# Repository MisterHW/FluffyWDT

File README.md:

# FluffyWDT
Raspberry Pi hardware watchdog with optional bluetooth SPP adapter

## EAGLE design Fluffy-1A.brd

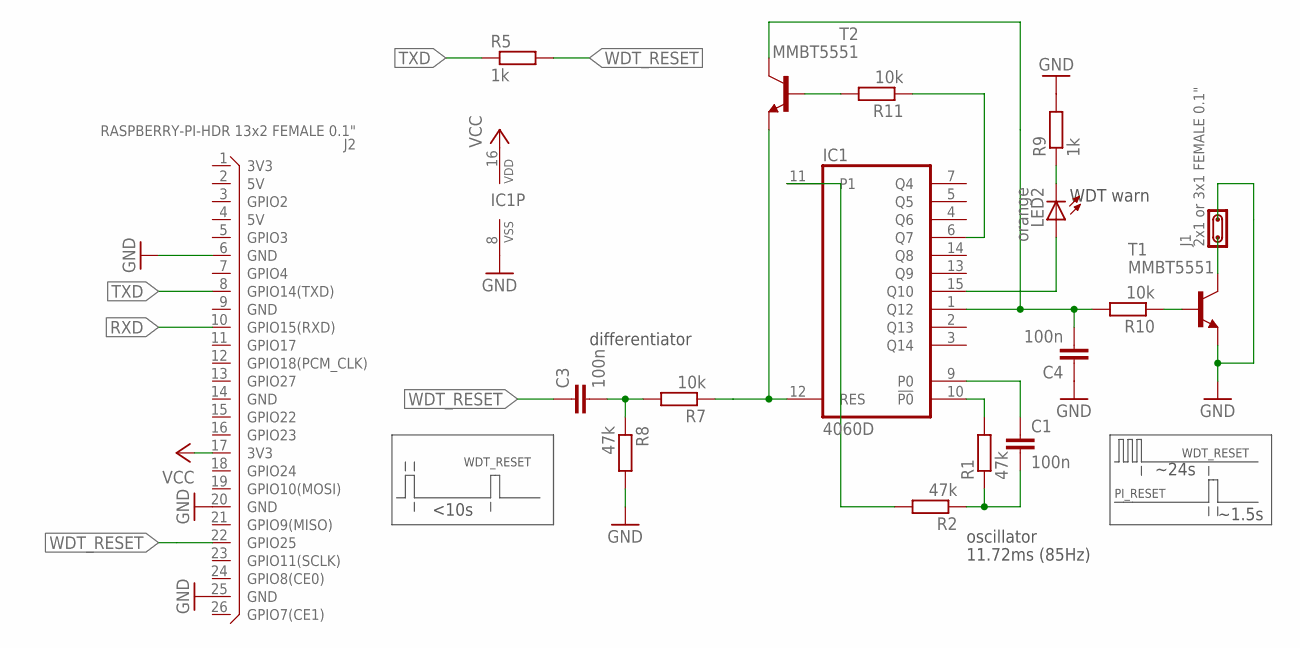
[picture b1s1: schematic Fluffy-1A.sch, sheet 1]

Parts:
C1, C3, C4: 100n; C0805K
IC1: 4060D; SO16
J1: 2x1 or 3x1 FEMALE 0.1"; JP02N
J2: RASPBERRY-PI-HDR 13x2 FEMALE 0.1"; X26R-DIL
LED2: orange; CHIPLED_0805
R1, R2, R8: 47k; R0805
R5, R9: 1k; R0805
R7, R10, R11: 10k; R0805
T1, T2: MMBT5551; SOT23-BEC

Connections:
GND: C4.1, IC1.8 (VSS), J1.2, J2.6 (GND), J2.20 (GND), J2.25 (GND), R8.2, R9.2, T1.E; also elsewhere on the board
unnamed: IC1.10 (!P0), R1.2
unnamed: C1.1, IC1.9 (P0)
unnamed: C1.2, R1.1, R2.1
unnamed: LED2.C, R9.1
unnamed: IC1.15 (Q10), LED2.A
unnamed: IC1.11 (P1), R2.2
unnamed: C3.2, R7.2, R8.1
unnamed: IC1.12 (RES), R7.1, T2.E
unnamed: R10.1, T1.B
unnamed: J1.1, T1.C
unnamed: C4.2, IC1.1 (Q12), R10.2, T2.C
unnamed: R11.2, T2.B
unnamed: IC1.6 (Q7), R11.1
RXD: J2.10 (GPIO15(RXD)); also elsewhere on the board
TXD: J2.8 (GPIO14(TXD)), R5.1; also elsewhere on the board
VCC: IC1.16 (VDD), J2.17 (3V3); also elsewhere on the board
WDT_RESET: C3.1, J2.22 (GPIO25), R5.2

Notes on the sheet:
differentiator
oscillator
11.72ms (85Hz)
WDT warn
<10s
~24s
~1.5s
WDT_RESET
PI_RESET

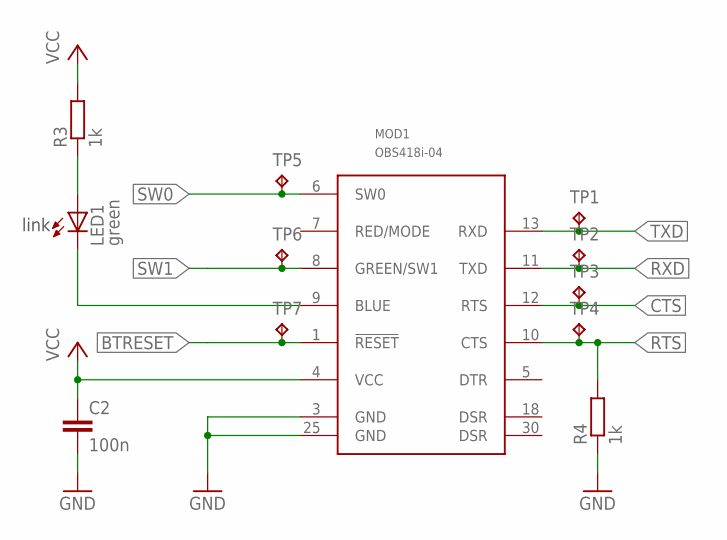
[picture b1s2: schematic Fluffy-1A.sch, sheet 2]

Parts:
C2: 100n; C0805K
LED1: green; CHIPLED_0805
MOD1: OBS418i-04; OBS4X1-NOHOLES
R3, R4: 1k; R0805
TP1, TP2, TP3, TP4, TP5, TP6, TP7: TPTP10SQ; TP10SQ

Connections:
BTRESET: MOD1.1 (!RESET), TP7.TP
CTS: MOD1.12 (RTS), TP3.TP
GND: C2.2, MOD1.3 (GND), MOD1.25 (GND), R4.1; also elsewhere on the board
unnamed: LED1.C, MOD1.9 (BLUE)
unnamed: LED1.A, R3.1
RTS: MOD1.10 (CTS), R4.2, TP4.TP
RXD: MOD1.11 (TXD), TP2.TP; also elsewhere on the board
SW0: MOD1.6 (SW0), TP5.TP
SW1: MOD1.8 (GREEN/SW1), TP6.TP
TXD: MOD1.13 (RXD), TP1.TP; also elsewhere on the board
VCC: C2.1, MOD1.4 (VCC), R3.2; also elsewhere on the board

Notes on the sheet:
link

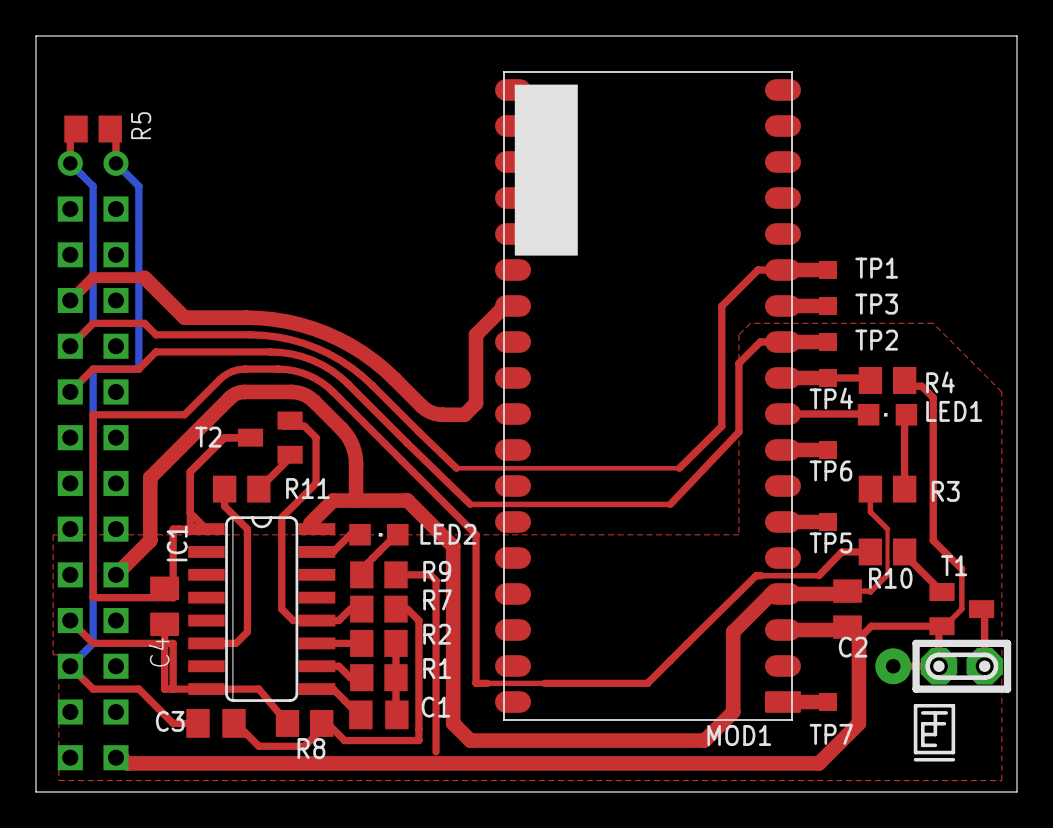
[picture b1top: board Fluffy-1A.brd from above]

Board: 2 copper layers, 54.5 x 42.0 mm, 30 parts (1 on the bottom side), 25 nets.

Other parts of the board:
U$1: DESIGNER

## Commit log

2018-04-18 initial commit
    board has been built and verified with an older Raspberry Pi board which has the 0.1" reset switch header.
    Use circuit at your own discretion.
